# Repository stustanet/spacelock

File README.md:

# Spacelock

StuStaNet Hackerspace Lock

# Firmware build instructions

The spacelock firmware can be configured for several use cases.

For each use case there is a config file in firmware/build_config.

In order to activate a config, `ln -s` the chosen config file to firmware/src/config.h

# How to adapt the config to your usecase

The firmware can be easily adapted to your hardware setup via the config file.
See [# Firmware build instructions] for more details on how to build.

Be aware that many parameters use "u" to indicate that the parameters decimal point is shifted by 1.000.000 this is done to prevent floating point operations. 

At most places where you see UREVS in the code, UREVS of the key are meanted.
`#define ENDSTOP_DEAD_WINDOW_UREVS 100'000` is one 10th of a key revolution.

## Feature Configuration
 You can decide how you want to use the spacelock board. Below are to configuraiton examples

### 1. Secure Door Unlocking via QR Code Sensor (StuSta)
In this case the board is autonomous and installed in combination with a UART QR-Code reader (`#define WITH_QRCODE`). The authentication happens via a web service and the unlock cmd is a HMAC signed QR-Code. In order to prevent e.g. replay attacks. The QR-Code holds a timestamp, and is only for valid for a limited time. Therefore an external time source is needed. In this case DCF77 this is. To prevent unwanted access set (`#define WITH_BACKDOOR 0`)

 ### 2. Unsecure UART Unlocking with Door Sensor (Biederstein)
In this case the board is controlled from a raspberry pi via UART. 
The raspberry pi does all the authorization and simply requests to open the door via UART with "open". To enable this functionality `#define WITH_BACKDOOR 1`. Furthermore a door sensor is used to check if the door is open and lock it, when it's closed (`#define WITH_DOOR_SENSOR 1`).  

## Motor Configuration
The motor should be any stepper that can be driven by the DRV8266.
The relevant motor parameters are:
- UREVS_PER_STEP eg. (1.000.000 / 200) for a motor that has 200 steps per revolution 
- MOTOR_REVS_TO_UKEY_REVS e.g. 4.000.000 for a 4:1 ratio (4 rotations of the motor is one rotation of the key)
    if you have a gearing between motor and key you can but the ratio hear.
- ENDSTOP_DEAD_WINDOW_UREVS e.g. 100'000 ignore the current for the first 10th of a key rotation (starting current)

## Lock Configuration
- UNLOCKING_UREVS maximum distance the key has to travel to turn from totally locked to unlocked
- UNLOCK_SPEED_UREVS_PER_SEC unlocking search speed in µrev/s (until a resistance is found)
- UNLOCK_FINAL_SPEED_UREVS_PER_SEC final unlocking speed in µrev/s 
- UNLOCK_HOLD_DELAY_US time to hold the lock open in µs. In our case the doors are spring loaded and will automatically swing open, when unlocked.
- UNLOCK_BACKING_UREVS µRevolutions to back the key up so the door is no longer forced open
- ENDSTOP_ROTATE_AFTER_EDGE_UREVS how far the key is to be turned after a resistance is found in µRevolutions.
- FORCE_UNLOCK_UREVS how far the key is to be forcefully turned in case gracefull unlocking fails in µRevolutions. The key is assumed to be allready close to the resistance. Thus, this should be not much more than ENDSTOP_ROTATE_AFTER_EDGE_UREVS.

## Locking Parameters
- LOCK_DELAY how long to wait until a closed door is locked (!!!TODO!!!) 
be ware something is broken here!!! in my experience a value of 5.000.000.000 relates to about 8 sec of delay.
- LOCKING_UREVS how far to lock e.g. 2 revolutions given in µRevolutions
- LOCKING_SPEED_UREVS_PER_SEC locking speed in µrev/s

## Door Sensor
- DOOR_OPEN_STATE either true or false depending on your sensor (default open, default closed)
- DOOR_PORT where you connected the sensor
- DOOR_PIN which pin you connected the sensor (be aware that the default location GPIOA PIN8 clashes with the DCF77)

## Edge Detection
These parameters depend on your motor and are best found by testing. You can use the debug output (`#define WITH_DEBUG_OUTPUT 1` and see hardware.cpp line 283) and the process_data.py to stream live current measurements into a csv and monitor it with e.g. PlotJuggler.

- EDGE_DETECTION_THRESHOLD_UA how many µA the current has to rise in order to be detected as an edge
- EDGE_STEEPNESS_THRESHOLD_A_PER_S how fast the current has to rise in A/s
- FALLING_EDGE_HEIGHT_RESET_THRESHOLD_RATIO This needs some explanation. The idea is that in theory we would only like to detect one continous edge and reset as soon as the current is dropping again. However sometimes there is a small drop in the current, but then it increases further. Actually this should be covered by EDGE_STEEPNESS_THRESHOLD_A_PER_S and should be removed in the future. For now a number of e.g. 4 means, that the edge is reset as soon as there is a 1/4 decrease from the previous max edge height. 

Apart from the edge detection there is also an current integral. power = current * voltage. Thus we use the current to estimate the power drawn from the motor and its integral to compute the dumped energy. This feature basically prevents the motor from drawing too much power for too much time. 
- IT_INTEGRAL_DECAY_UA basically gives the power draw in normal operation, any excess current is then cumulated
- IT_INTEGRAL_THRESHOLD_UA_US a "energy" threshold in µA µs for the endstop detector

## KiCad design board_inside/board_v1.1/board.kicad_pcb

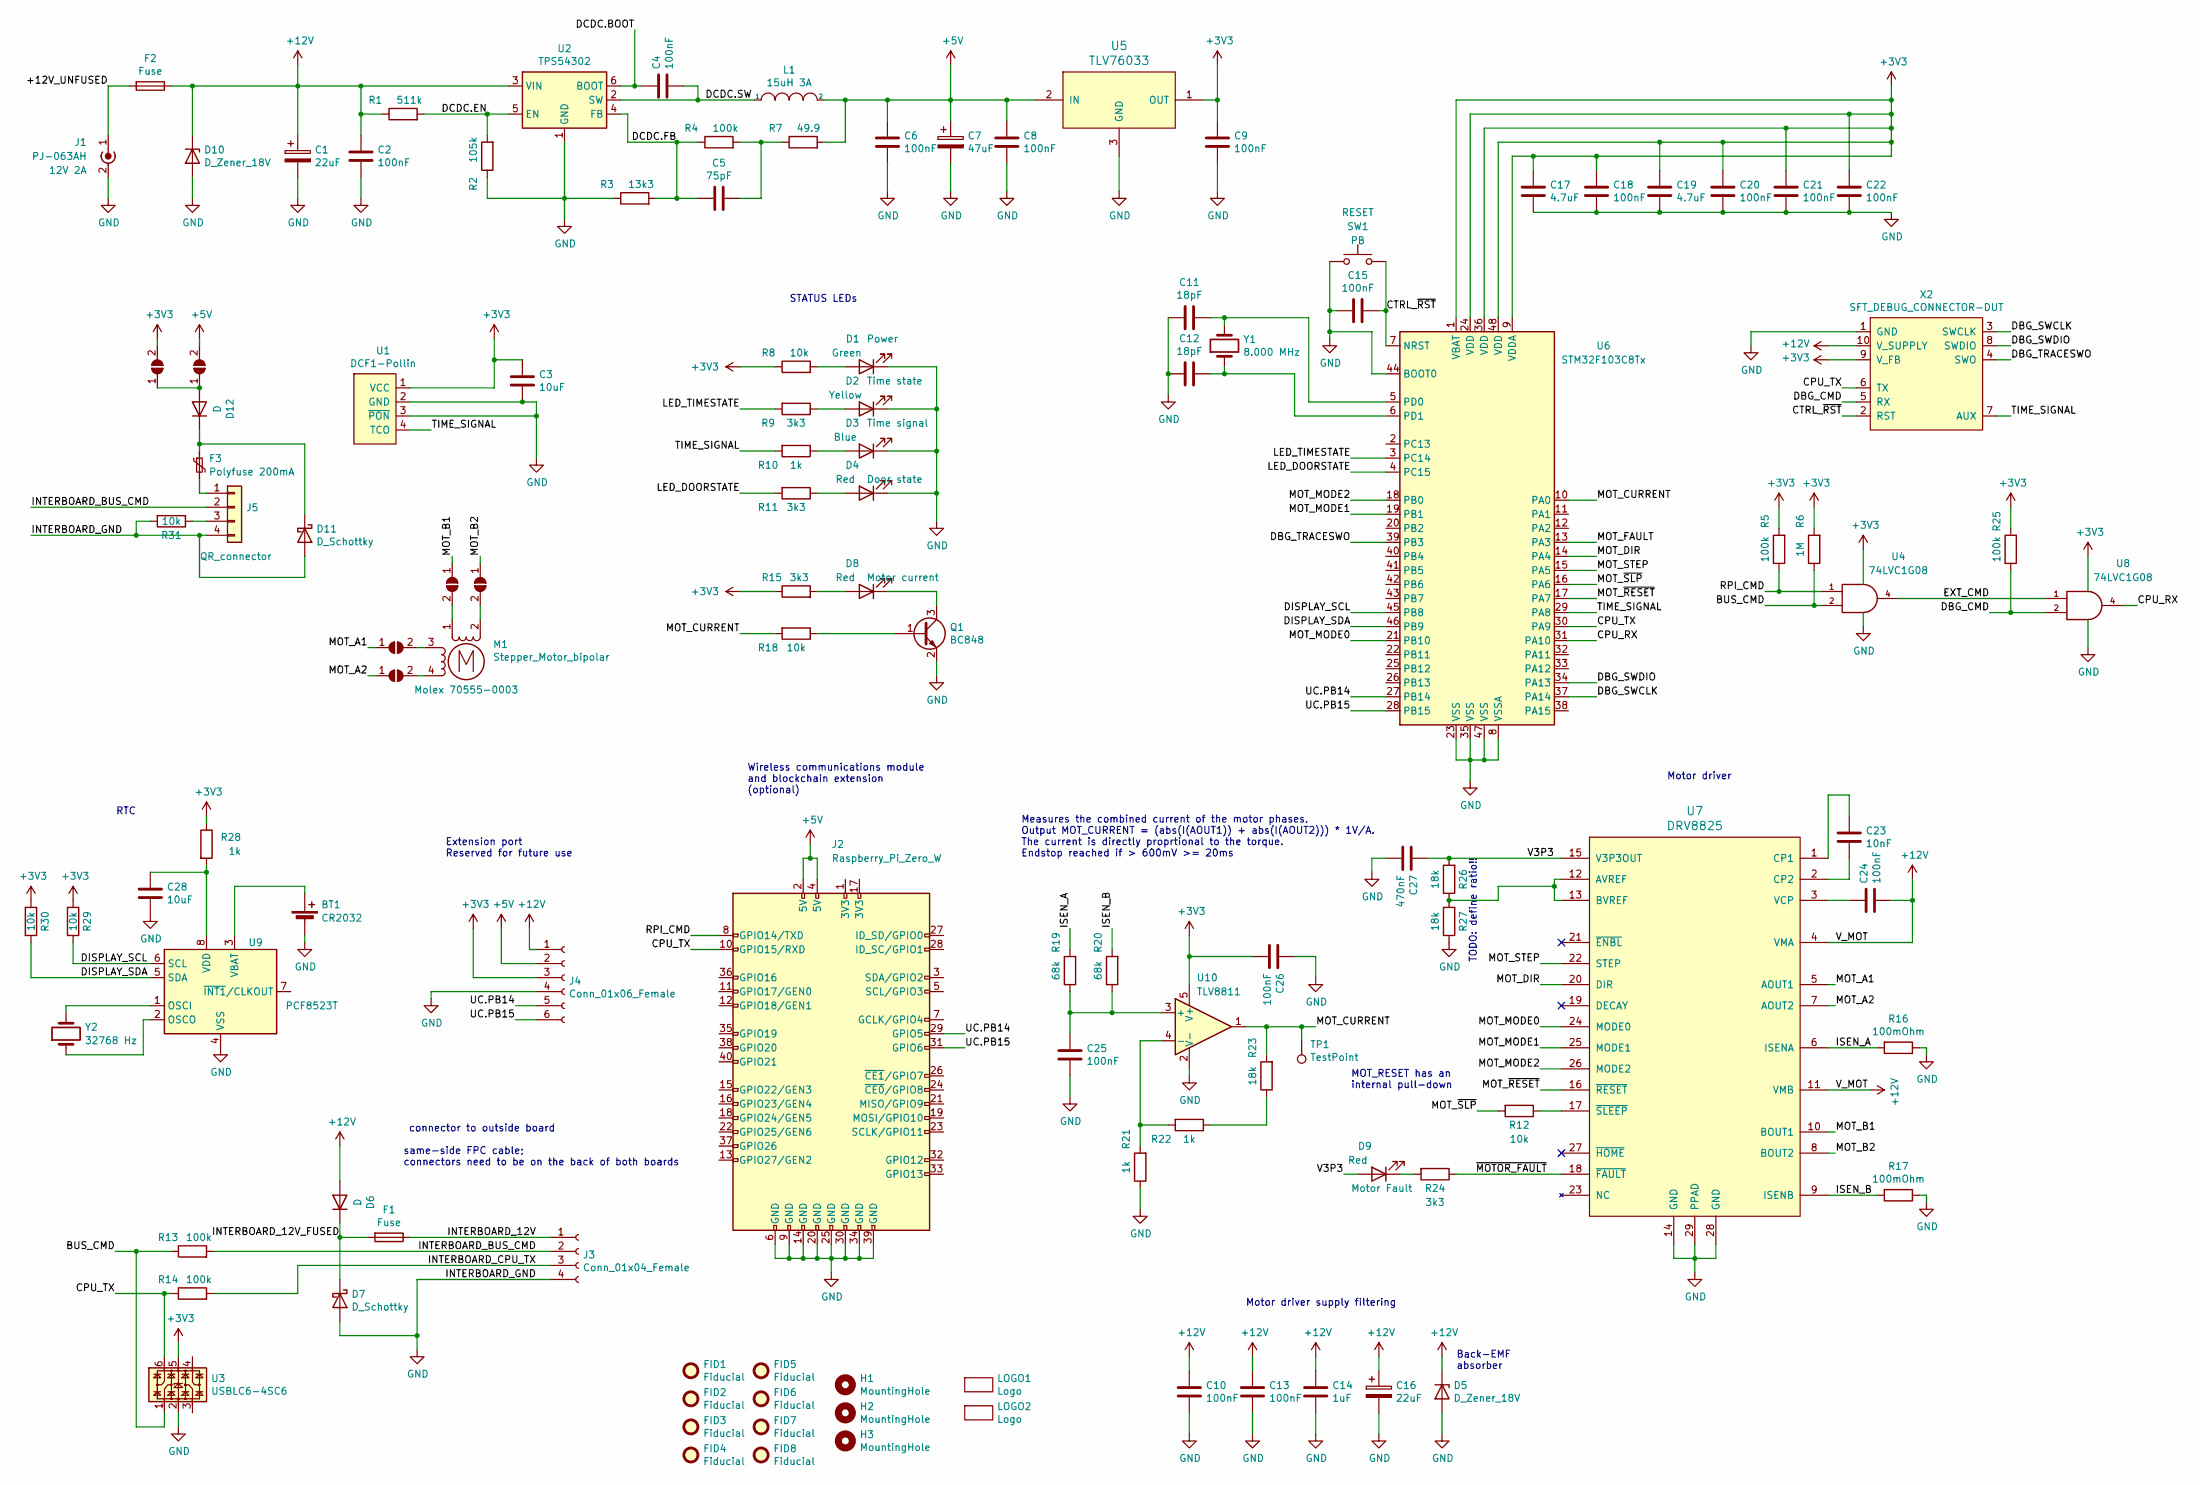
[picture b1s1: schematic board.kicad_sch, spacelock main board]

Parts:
BT1: CR2032; BatteryHolder_Keystone_3000_1x12mm; MPN Keystone 3000
C1, C16: 22uF; C_1206_3216Metric_Pad1.33x1.80mm_HandSolder; Rating 25V; MPN generic C%f %v %r
C2, C4, C6, C8, C9, C10, C13, C15, C18, C20, C21, C22, C24, C25, C26: 100nF; C_0603_1608Metric_Pad1.08x0.95mm_HandSolder; MPN generic C%f %v %r
C3, C28: 10uF; C_0603_1608Metric_Pad1.08x0.95mm_HandSolder; Rating 6.3V; MPN generic C%f %v %r
C5: 75pF; C_0603_1608Metric_Pad1.08x0.95mm_HandSolder; MPN generic C%f %v %r
C7: 47uF; C_1206_3216Metric_Pad1.33x1.80mm_HandSolder; Rating 6.3V; MPN generic C%f %v %r
C11, C12: 18pF; C_0603_1608Metric_Pad1.08x0.95mm_HandSolder; MPN generic C%f %v %r
C14: 1uF; C_0603_1608Metric_Pad1.08x0.95mm_HandSolder; MPN generic C%f %v %r
C17, C19: 4.7uF; C_0603_1608Metric_Pad1.08x0.95mm_HandSolder; Rating 6.3V; MPN generic C%f %v %r
C23: 10nF; C_0603_1608Metric_Pad1.08x0.95mm_HandSolder; MPN generic C%f %v %r
C27: 470nF; C_0603_1608Metric_Pad1.08x0.95mm_HandSolder; Rating 6.3V; MPN generic C%f %v %r
D1: Green; LED_0805_2012Metric_Pad1.15x1.40mm_HandSolder; MPN Wuerth 150080GS75000
D2: Yellow; LED_0805_2012Metric_Pad1.15x1.40mm_HandSolder; MPN Wuerth 150080YS75000
D3: Blue; LED_0805_2012Metric_Pad1.15x1.40mm_HandSolder; MPN Wuerth 150080BS75000
D4, D8, D9: Red; LED_0805_2012Metric_Pad1.15x1.40mm_HandSolder; MPN Wuerth 150080RS75000
D5, D10: D_Zener_18V; D_MiniMELF_Handsoldering; MPN generic ZMM5248B
D6, D12: D; D_SMB; MPN Rectron HFM208-W
D7, D11: D_Schottky; D_SOD-123; MPN Rectron 2SS100L-W
F1, F2: Fuse; Schurter-OGN-SMD; MPN Schurter OGN SMD
F3: Polyfuse 200mA; R_1210_3225Metric; MPN Littlefuse 1206L020YR
FID1, FID2, FID3, FID4, FID5, FID6, FID7, FID8: Fiducial; Fiducial_1mm_Mask2mm
H1, H2, H3: MountingHole; MountingHole_3.2mm_M3
J1: PJ-063AH; BarrelJack_CUI_PJ-063AH_Horizontal; MPN CUI PJ-063AH
J2: Raspberry_Pi_Zero_W; Raspberry_Pi_Zero_Socketed_THT_FaceDown_MountingHoles
J3: Conn_01x04_Female; Wuerth-686104188622; MPN Wuerth 686104188622
J4: Conn_01x06_Female; PinSocket_1x06_P2.54mm_Vertical
J5: QR_connector; PinHeader_1x04_P2.54mm_Vertical; MPN generic header-2.54mm
JP1, JP2, JP3, JP4, JP5, JP6: SolderJumper_2_Open; SolderJumper-2_P1.3mm_Open_TrianglePad1.0x1.5mm
L1: 15uH 3A; SRN8040TA; MPN Bourns SRN8040TA-150M
LOGO1: Logo; LOGO
LOGO2: Logo; LOGO_CU_070
M1: Stepper_Motor_bipolar; Molex-70555-0003; MPN Molex 70555-0003
Q1: BC848; SOT-23; MPN generic BC848B
R1: 511k; R_0603_1608Metric_Pad0.98x0.95mm_HandSolder; MPN generic R%f %v %r
R2: 105k; R_0603_1608Metric_Pad0.98x0.95mm_HandSolder; MPN generic R%f %v %r
R3: 13k3; R_0603_1608Metric_Pad0.98x0.95mm_HandSolder; MPN generic R%f %v %r
R4, R5, R13, R14, R25: 100k; R_0603_1608Metric_Pad0.98x0.95mm_HandSolder; MPN generic R%f %v %r
R6: 1M; R_0603_1608Metric_Pad0.98x0.95mm_HandSolder; MPN generic R%f %v %r
R7: 49.9; R_0603_1608Metric_Pad0.98x0.95mm_HandSolder; MPN generic R%f %v %r
R8, R12, R18, R29, R30, R31: 10k; R_0603_1608Metric_Pad0.98x0.95mm_HandSolder; MPN generic R%f %v %r
R9, R11, R15, R24: 3k3; R_0603_1608Metric_Pad0.98x0.95mm_HandSolder; MPN generic R%f %v %r
R10, R21, R22, R28: 1k; R_0603_1608Metric_Pad0.98x0.95mm_HandSolder; MPN generic R%f %v %r
R16, R17: 100mOhm; R_2512_6332Metric; MPN Yageo PT2512FK-7W0R1L
R19, R20: 68k; R_0603_1608Metric_Pad0.98x0.95mm_HandSolder; MPN generic R%f %v %r
R23, R26, R27: 18k; R_0603_1608Metric_Pad0.98x0.95mm_HandSolder; MPN generic R%f %v %r
SW1: PB; SW_PUSH_6mm_H4.3mm; MPN Panasonic EVQPAE05R
TP1: TestPoint; TestPoint_Pad_D1.5mm
U1: DCF1-Pollin; MPN Pollin DCF1
U2: TPS54302; SOT-23-6; MPN TI TPS54302DDC
U3: USBLC6-4SC6; SOT-23-6; MPN ST USBLC6-4SC6
U4, U8: 74LVC1G08; SOT-23-5_HandSoldering; MPN TI 74LVC1G08DBV
U5: TLV76033; SOT-23; MPN TI TLV76033DBZ
U6: STM32F103C8Tx; LQFP-48_7x7mm_P0.5mm; MPN ST STM32F103C8T6
U7: DRV8825; HTSSOP-28-1EP_4.4x9.7mm_P0.65mm_EP3.4x9.5mm_ThermalVias; MPN TI DRV8825PWP
U9: PCF8523T; SOIC-8_3.9x4.9mm_P1.27mm; MPN NXP PCF8523T
U10: TLV8811; SOT-23-5_HandSoldering; MPN TI TLV8811DBV
X2: SFT_DEBUG_CONNECTOR-DUT; Tag-Connect_TC2050-IDC-FP_2x05_P1.27mm_Vertical
Y1: 8.000 MHz; Crystal_HC49-U_Vertical; MPN ZheJiang B08000J065
Y2: 32768 Hz; Crystal_SMD_EuroQuartz_EQ161-2Pin_3.2x1.5mm_HandSoldering; MPN MicroCrystal CM7V-T1A-LOW-ESR-32.768KHZ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

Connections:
+3V3: C3.1, C9.1, C17.1, C18.1, C19.1, C20.1, C21.1, C22.1, C26.2, J4.3, JP6.2 (B), R5.2, R6.2, R8.1, R15.1, R25.2, R28.1, R29.1, R30.1, U1.1 (VCC), U3.5, U4.5 (VCC), U5.1 (OUT), U6.1 (VBAT), U6.9 (VDDA), U6.24 (VDD), U6.36 (VDD), U6.48 (VDD), U8.5 (VCC), U10.5 (V+), X2.9 (V_FB)
+5V: C6.1, C7.1, C8.1, J2.2 (5V), J2.4 (5V), J4.2, JP5.2 (B), L1.2, R7.2, U5.2 (IN)
+12V: C1.1, C2.1, C10.1, C13.1, C14.1, C16.1, C24.2, D5.1 (K), D6.2 (A), D10.1 (K), F2.1, J4.1, R1.1, U2.3 (VIN), U7.4 (VMA), U7.11 (VMB), X2.10 (V_SUPPLY)
/+12V_UNFUSED: F2.2, J1.1 (In)
/BUS_CMD: R6.1, R13.1, U3.1, U4.2
/CPU_RX: U6.31 (PA10), U8.4
/CPU_TX: J2.10 (GPIO15/RXD), R14.1, U3.6, U6.30 (PA9), X2.6 (TX)
/CTRL_~RST: C15.1, SW1.2, U6.7 (NRST), X2.2 (RST)
/DBG_CMD: R25.1, U8.2, X2.5 (RX)
/DBG_SWCLK: U6.37 (PA14), X2.3 (SWCLK)
/DBG_SWDIO: U6.34 (PA13), X2.8 (SWDIO)
/DBG_TRACESWO: U6.39 (PB3), X2.4 (SWO)
/DCDC.BOOT: C4.1, U2.6 (BOOT)
/DCDC.EN: R1.2, R2.2, U2.5 (EN)
/DCDC.FB: C5.2, R3.2, R4.1, U2.4 (FB)
/DCDC.SW: C4.2, L1.1, U2.2 (SW)
/DISPLAY_SCL: R29.2, U6.45 (PB8), U9.6 (SCL)
/DISPLAY_SDA: R30.2, U6.46 (PB9), U9.5 (SDA)
/EXT_CMD: U4.4, U8.1
/INTERBOARD_12V: F1.1, J3.1
/INTERBOARD_12V_FUSED: D6.1 (K), D7.1 (K), F1.2
/INTERBOARD_BUS_CMD: J3.2, J5.2, R13.2
/INTERBOARD_CPU_TX: J3.3, R14.2
/ISEN_A: R16.2, R19.2, U7.6 (ISENA)
/ISEN_B: R17.2, R20.2, U7.9 (ISENB)
/LED_DOORSTATE: R11.2, U6.4 (PC15)
/LED_TIMESTATE: R9.2, U6.3 (PC14)
/MOT_A1: JP1.1 (A), U7.5 (AOUT1)
/MOT_A2: JP2.1 (A), U7.7 (AOUT2)
/MOT_B1: JP3.1 (A), U7.10 (BOUT1)
/MOT_B2: JP4.1 (A), U7.8 (BOUT2)
/MOT_CURRENT: R18.2, R23.2, TP1.1, U6.10 (PA0), U10.1
/MOT_DIR: U6.14 (PA4), U7.20 (DIR)
/MOT_FAULT: U6.13 (PA3)
/MOT_MODE0: U6.21 (PB10), U7.24 (MODE0)
/MOT_MODE1: U6.19 (PB1), U7.25 (MODE1)
/MOT_MODE2: U6.18 (PB0), U7.26 (MODE2)
/MOT_STEP: U6.15 (PA5), U7.22 (STEP)
/MOT_~RESET: U6.17 (PA7), U7.16 (~RESET)
/MOT_~SLP: R12.2, U6.16 (PA6)
/RPI_CMD: J2.8 (GPIO14/TXD), R5.1, U4.1
/TIME_SIGNAL: R10.2, U1.4 (TCO), U6.29 (PA8), X2.7 (AUX)
/UC.PB14: J2.29 (GPIO5), J4.5, U6.27 (PB14)
/UC.PB15: J2.31 (GPIO6), J4.6, U6.28 (PB15)
/V3P3: C27.1, D9.2 (A), R26.2, U7.15 (V3P3OUT)
/~MOTOR_FAULT: R24.1, U7.18 (~FAULT)
GND: BT1.2 (-), C1.2, C2.2, C3.2, C6.2, C7.2, C8.2, C9.2, C10.2, C11.2, C12.2, C13.2, C14.2, C15.2, C16.2, C17.2, C18.2, C19.2, C20.2, C21.2, C22.2, C25.2, C26.1, C27.2, C28.2, D1.1 (K), D2.1 (K), D3.1 (K), D4.1 (K), D5.2 (A), D7.2 (A), D10.2 (A), D11.2 (A), J1.2 (Ext), J2.6 (GND), J2.9 (GND), J2.14 (GND), J2.20 (GND), J2.25 (GND), J2.30 (GND), J2.34 (GND), J2.39 (GND), J3.4, J4.4, J5.4, Q1.2 (E), R2.1, R3.1, R16.1, R17.1, R21.1, R27.1, R31.2, SW1.1, U1.2 (GND), U1.3 (~PON), U2.1 (GND), U3.2, U4.3 (GND), U5.3 (GND), U6.8 (VSSA), U6.23 (VSS), U6.35 (VSS), U6.44 (BOOT0), U6.47 (VSS), U7.14 (GND), U7.28 (GND), U7.29 (PPAD), U8.3 (GND), U9.4 (VSS), U10.2 (V-), X2.1 (GND)
unnamed: BT1.1 (+), U9.3 (VBAT)
unnamed: C5.1, R4.2, R7.1
unnamed: D1.2 (A), R8.2
unnamed: D2.2 (A), R9.1
unnamed: D3.2 (A), R10.1
unnamed: D4.2 (A), R11.1
unnamed: D8.2 (A), R15.2
unnamed: D8.1 (K), Q1.3 (C)
unnamed: D9.1 (K), R24.2
unnamed: D11.1 (K), D12.1 (K), F3.1
unnamed: D12.2 (A), JP5.1 (A), JP6.1 (A)
unnamed: F3.2, J5.1
unnamed: J5.3, R31.1
unnamed: JP1.2 (B), M1.3
unnamed: JP2.2 (B), M1.4
unnamed: JP3.2 (B), M1.1
unnamed: JP4.2 (B), M1.2 (-)
unnamed: Q1.1 (B), R18.1
unnamed: R22.1, R23.1
unnamed: C11.1, U6.5 (PD0), Y1.2
unnamed: C12.1, U6.6 (PD1), Y1.1
unnamed: R26.1, R27.2, U7.12 (AVREF), U7.13 (BVREF)
unnamed: C23.1, U7.1 (CP1)
unnamed: C23.2, U7.2 (CP2)
unnamed: C24.1, U7.3 (VCP)
unnamed: R12.1, U7.17 (~SLEEP)
unnamed: U9.1 (OSCI), Y2.2
unnamed: U9.2 (OSCO), Y2.1
unnamed: C28.1, R28.2, U9.8 (VDD)
unnamed: C25.1, R19.1, R20.1, U10.3 (+)
unnamed: R21.2, R22.2, U10.4 (-)

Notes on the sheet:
Measures the combined current of the motor phases. Output MOT_CURRENT = (abs(I(AOUT1)) + abs(I(AOUT2))) * 1V/A. The current is directly proprtional to the torque. Endstop reached if > 600mV >= 20ms
MOT_RESET has an internal pull-down
Back-EMF absorber
Extension port Reserved for future use
Motor driver supply filtering
STATUS LEDs
RTC
Wireless communications module and blockchain extension (optional)
Motor driver
TODO: define ratio!!
connector to outside board same-side FPC cable; connectors need to be on the back of both boards

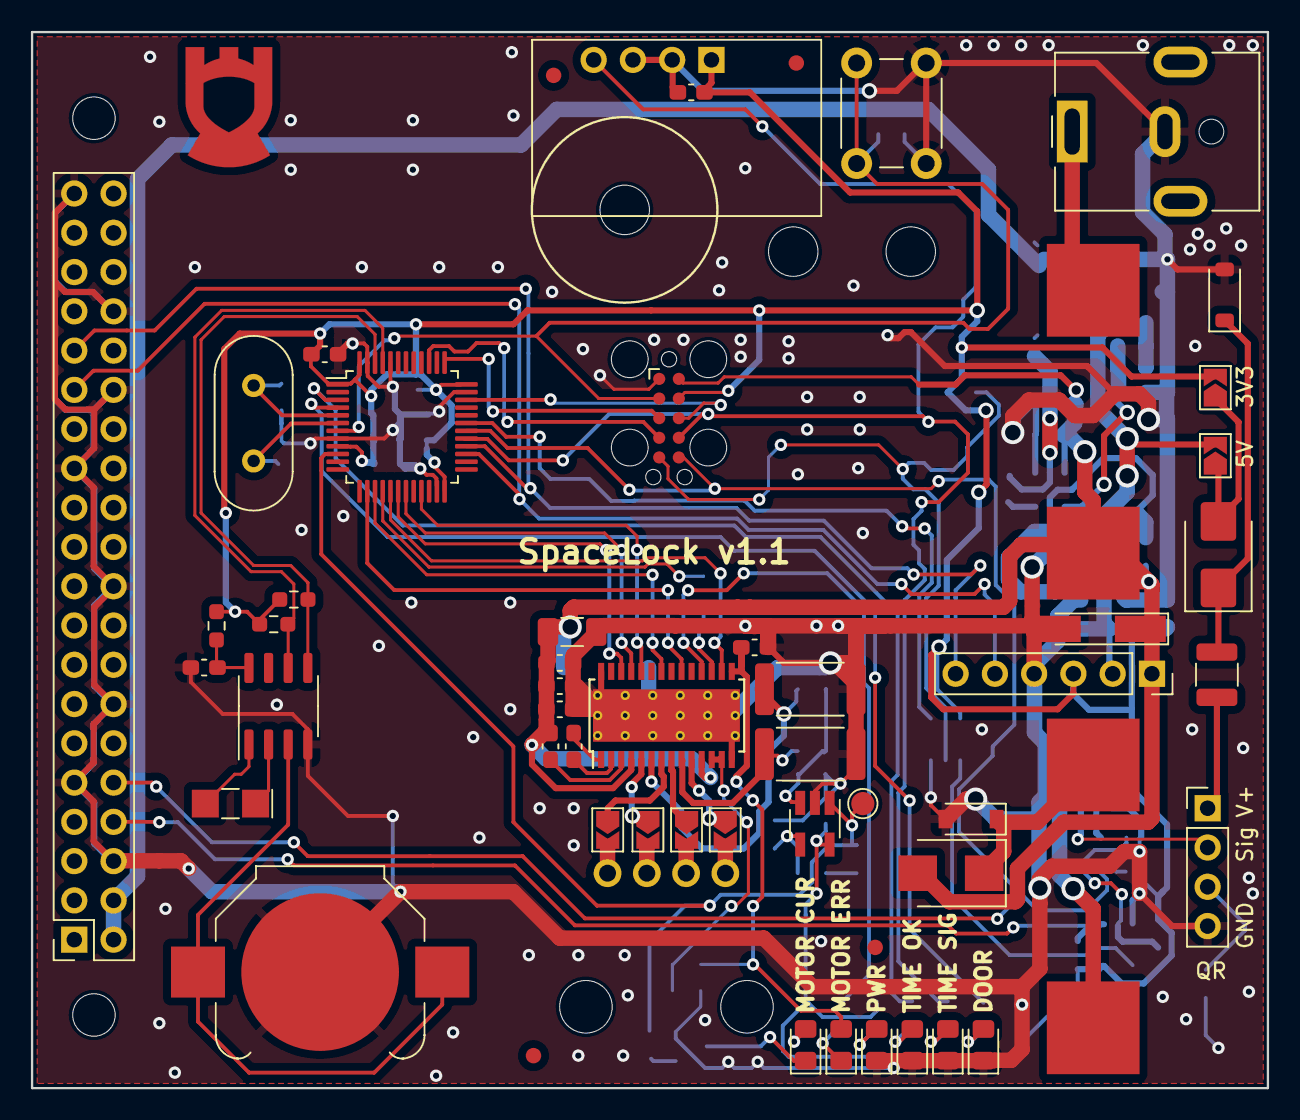
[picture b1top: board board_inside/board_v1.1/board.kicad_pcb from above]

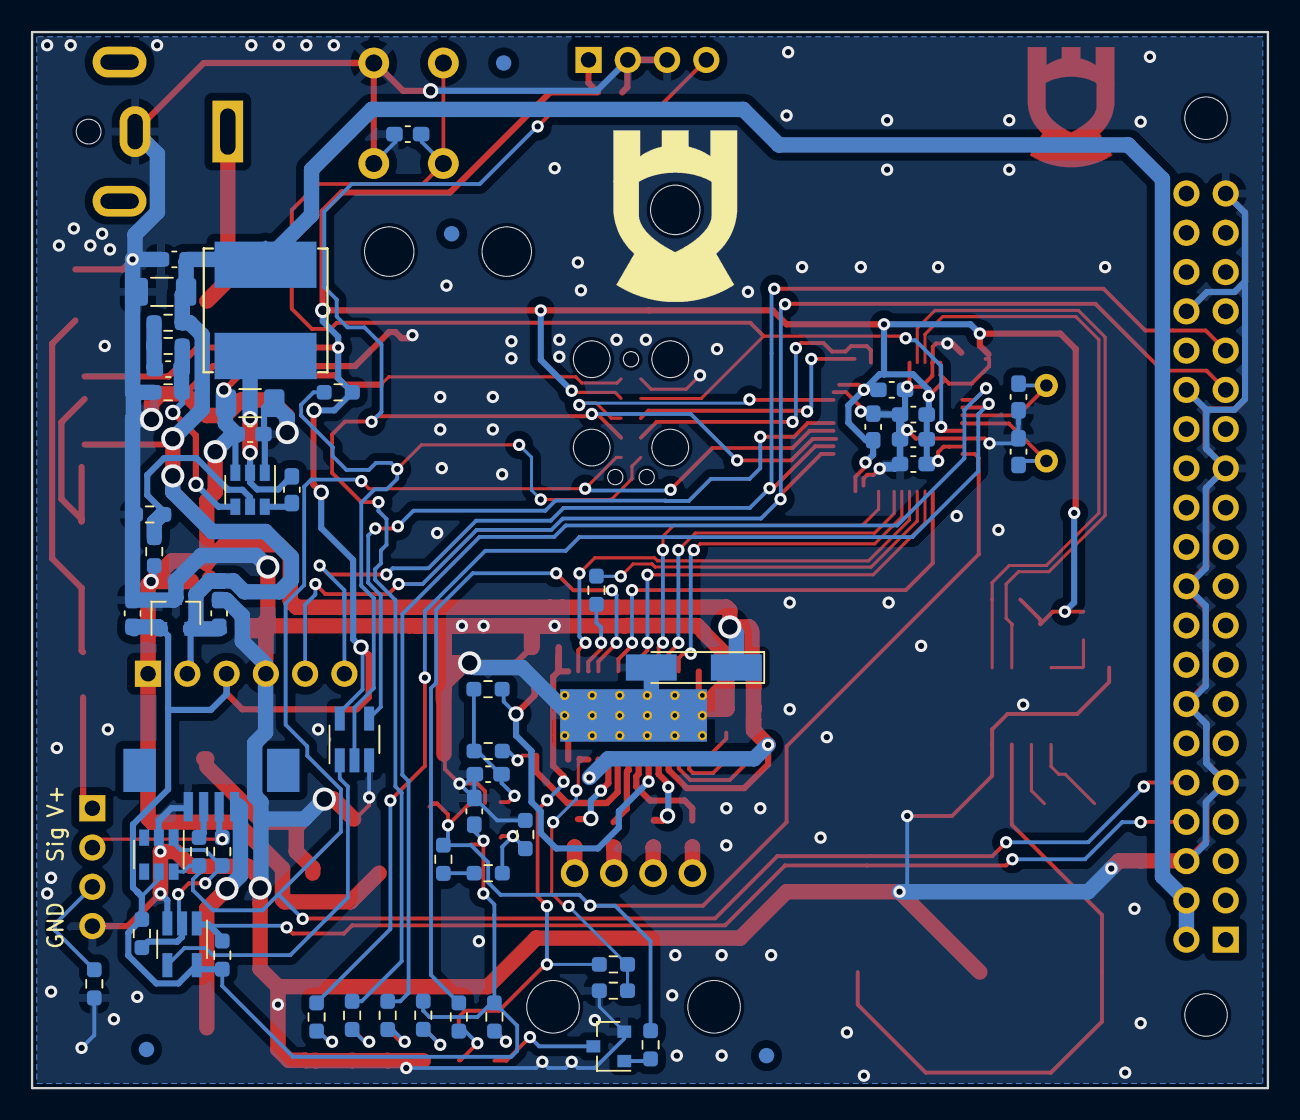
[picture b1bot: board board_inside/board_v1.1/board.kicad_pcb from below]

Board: 2 copper layers, 79.9 x 68.3 mm, 117 parts (58 on the bottom side), 77 nets.

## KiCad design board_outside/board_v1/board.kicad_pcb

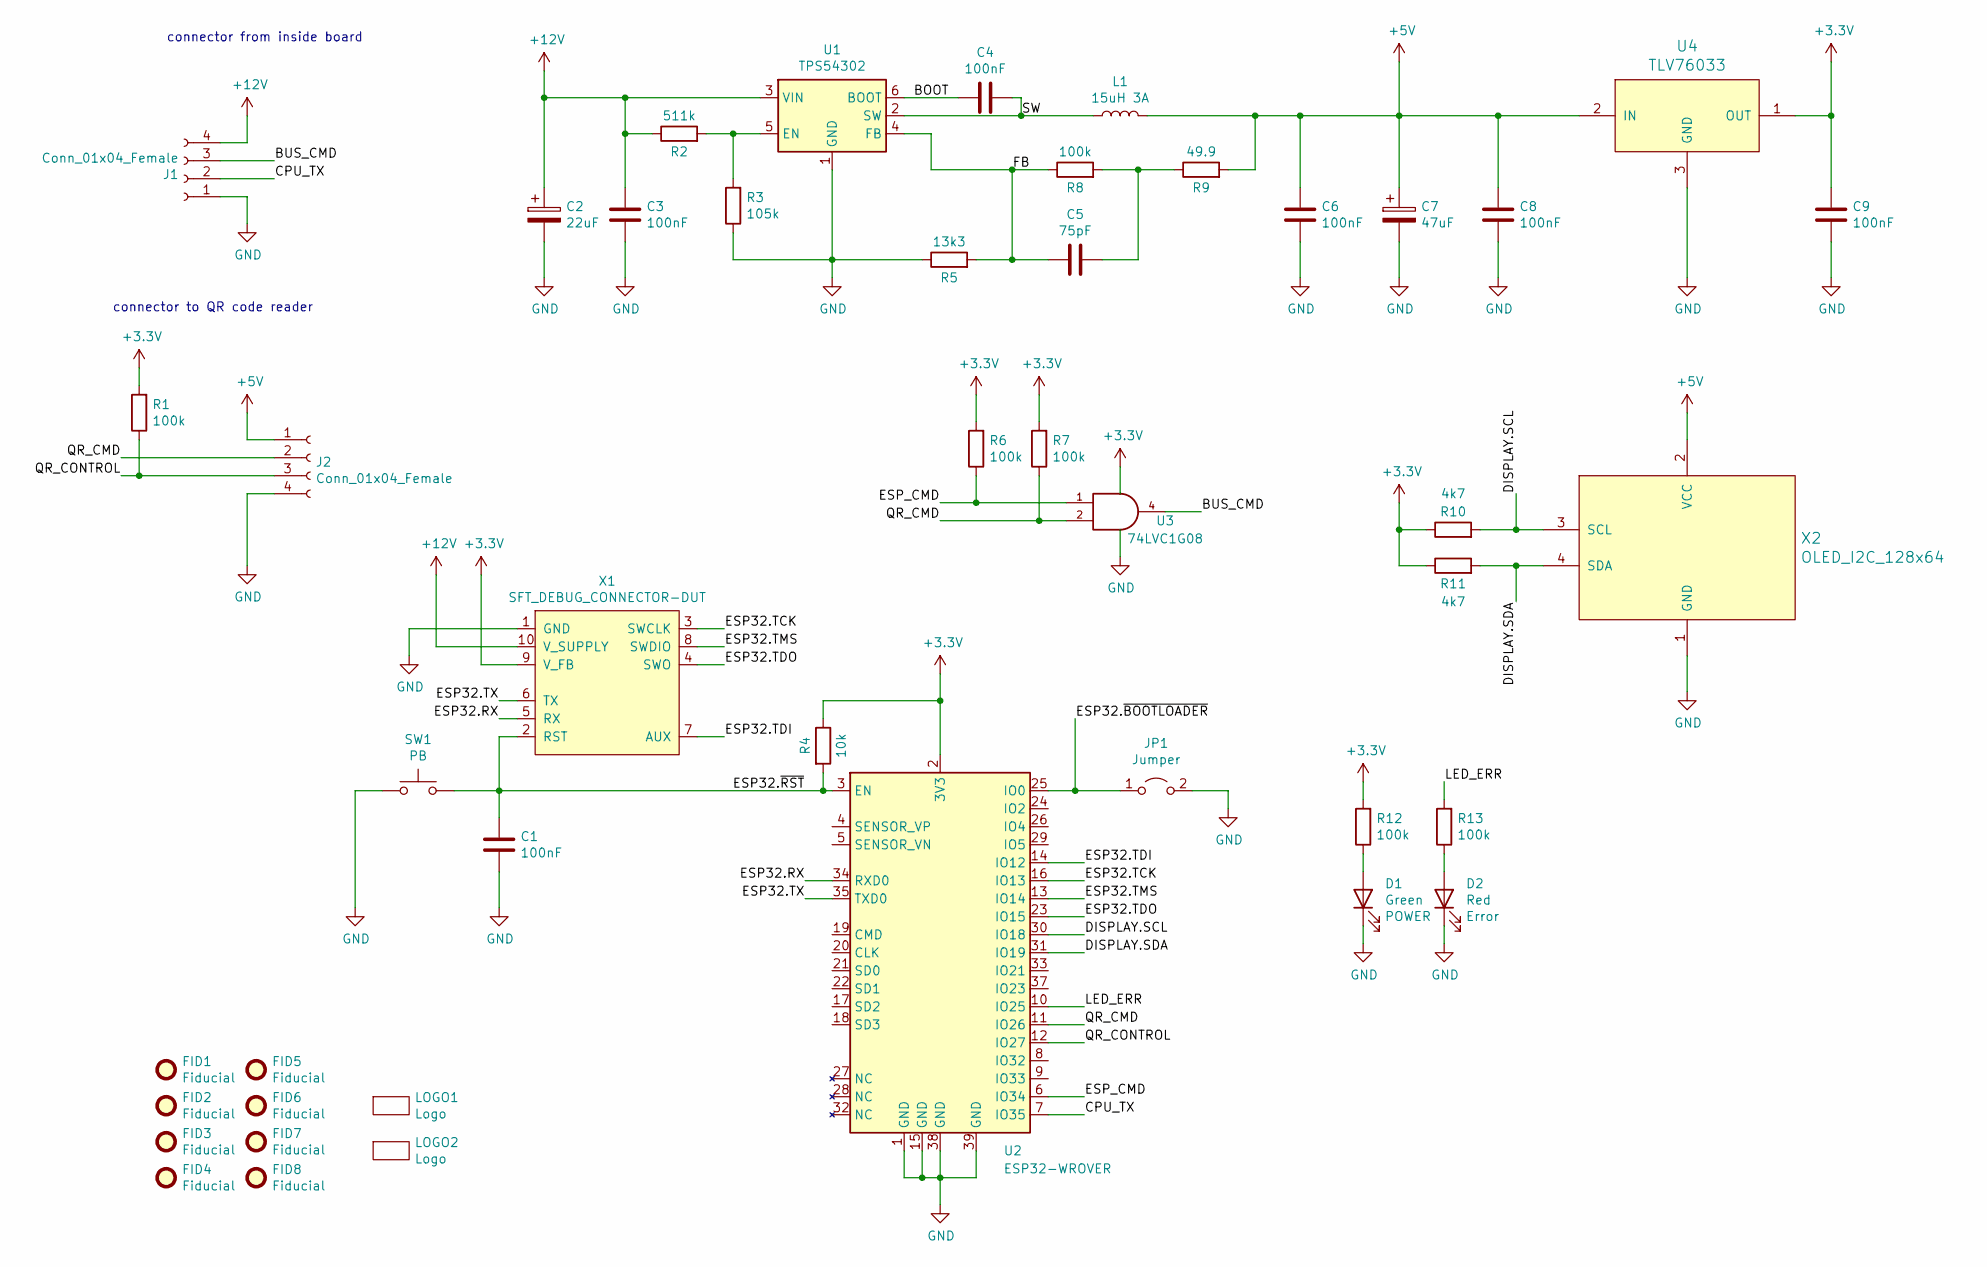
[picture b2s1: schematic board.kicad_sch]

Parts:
C1, C3, C4, C6, C8, C9: 100nF; C_0603_1608Metric_Pad1.08x0.95mm_HandSolder; MPN generic C%f %v %r
C2: 22uF; C_1206_3216Metric_Pad1.33x1.80mm_HandSolder; Rating 25V; MPN generic C%f %v %r
C5: 75pF; C_0603_1608Metric_Pad1.08x0.95mm_HandSolder; MPN generic C%f %v %r
C7: 47uF; C_1206_3216Metric_Pad1.33x1.80mm_HandSolder; Rating 6.3V; MPN generic C%f %v %r
D1: Green; LED_0805_2012Metric_Pad1.15x1.40mm_HandSolder; MPN Wuerth 150080GS75000
D2: Red; LED_0805_2012Metric_Pad1.15x1.40mm_HandSolder; MPN Wuerth 150080RS75000
FID1, FID2, FID3, FID4, FID5, FID6, FID7, FID8: Fiducial; Fiducial_1mm_Mask2mm
J1: Conn_01x04_Female; Wuerth-686104188622; MPN Wuerth 686104188622
J2: Conn_01x04_Female; PinSocket_1x04_P2.54mm_Vertical; MPN generic header-2.54mm
JP1: Jumper; PinHeader_1x02_P2.54mm_Vertical
L1: 15uH 3A; SRN8040TA; MPN Bourns SRN8040TA-150M
LOGO1: Logo; LOGO_CU_070
LOGO2: Logo; LOGO
R1, R6, R7, R8, R12, R13: 100k; R_0603_1608Metric_Pad0.98x0.95mm_HandSolder; MPN generic R%f %v %r
R2: 511k; R_0603_1608Metric_Pad0.98x0.95mm_HandSolder; MPN generic R%f %v %r
R3: 105k; R_0603_1608Metric_Pad0.98x0.95mm_HandSolder; MPN generic R%f %v %r
R4: 10k; R_0603_1608Metric_Pad0.98x0.95mm_HandSolder; MPN generic R%f %v %r
R5: 13k3; R_0603_1608Metric_Pad0.98x0.95mm_HandSolder; MPN generic R%f %v %r
R9: 49.9; R_0603_1608Metric_Pad0.98x0.95mm_HandSolder; MPN generic R%f %v %r
R10, R11: 4k7; R_0603_1608Metric_Pad0.98x0.95mm_HandSolder; MPN generic R%f %v %r
SW1: PB; SW_PUSH_6mm_H4.3mm; MPN Panasonic EVQPAE05R
U1: TPS54302; SOT-23-6; MPN TI TPS54302DDC
U2: ESP32-WROVER; MPN Espressif ESP32-WROVER
U3: 74LVC1G08; SOT-23-5_HandSoldering; MPN TI 74LVC1G08DBV
U4: TLV76033; SOT-23; MPN TI TLV76033DBZ
X1: SFT_DEBUG_CONNECTOR-DUT; Tag-Connect_TC2050-IDC-FP_2x05_P1.27mm_Vertical
X2: OLED_I2C_128x64; OLED_128x64_096in; MPN generic I2C-OLED-128x64

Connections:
+3V3: C9.1, R1.2, R4.1, R6.2, R7.2, R10.1, R11.1, R12.2, U2.2 (3V3), U3.5 (VCC), U4.1 (OUT), X1.9 (V_FB)
+5V: C6.1, C7.1, C8.1, J2.1, L1.2, R9.2, U4.2 (IN), X2.2 (VCC)
+12V: C2.1, C3.1, J1.4, R2.1, U1.3 (VIN), X1.10 (V_SUPPLY)
/BOOT: C4.2, U1.6 (BOOT)
/BUS_CMD: J1.3, U3.4
/CPU_TX: J1.2, U2.7 (IO35)
/DISPLAY.SCL: R10.2, U2.30 (IO18), X2.3 (SCL)
/DISPLAY.SDA: R11.2, U2.31 (IO19), X2.4 (SDA)
/ESP32.RX: U2.34 (RXD0), X1.5 (RX)
/ESP32.TCK: U2.16 (IO13), X1.3 (SWCLK)
/ESP32.TDI: U2.14 (IO12), X1.7 (AUX)
/ESP32.TDO: U2.23 (IO15), X1.4 (SWO)
/ESP32.TMS: U2.13 (IO14), X1.8 (SWDIO)
/ESP32.TX: U2.35 (TXD0), X1.6 (TX)
/ESP32.~BOOTLOADER: JP1.1 (A), U2.25 (IO0)
/ESP32.~RST: C1.1, R4.2, SW1.2, U2.3 (EN), X1.2 (RST)
/ESP_CMD: R6.1, U2.6 (IO34), U3.1
/FB: C5.2, R5.2, R8.1, U1.4 (FB)
/LED_ERR: R13.2, U2.10 (IO25)
/QR_CMD: J2.2, R7.1, U2.11 (IO26), U3.2
/QR_CONTROL: J2.3, R1.1, U2.12 (IO27)
/SW: C4.1, L1.1, U1.2 (SW)
GND: C1.2, C2.2, C3.2, C6.2, C7.2, C8.2, C9.2, D1.1 (K), D2.1 (K), J1.1, J2.4, JP1.2 (B), R3.1, R5.1, SW1.1, U1.1 (GND), U2.1 (GND), U2.15 (GND), U2.38 (GND), U2.39 (GND), U3.3 (GND), U4.3 (GND), X1.1 (GND), X2.1 (GND)
unnamed: C5.1, R8.2, R9.1
unnamed: D1.2 (A), R12.1
unnamed: D2.2 (A), R13.1
unnamed: R2.2, R3.2, U1.5 (EN)

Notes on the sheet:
connector to QR code reader
connector from inside board

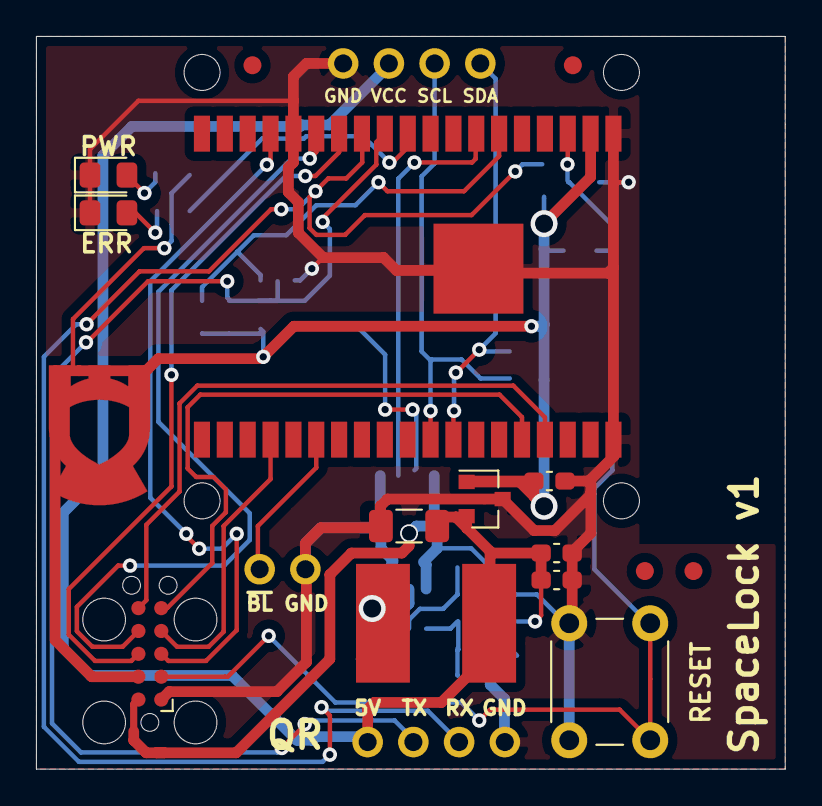
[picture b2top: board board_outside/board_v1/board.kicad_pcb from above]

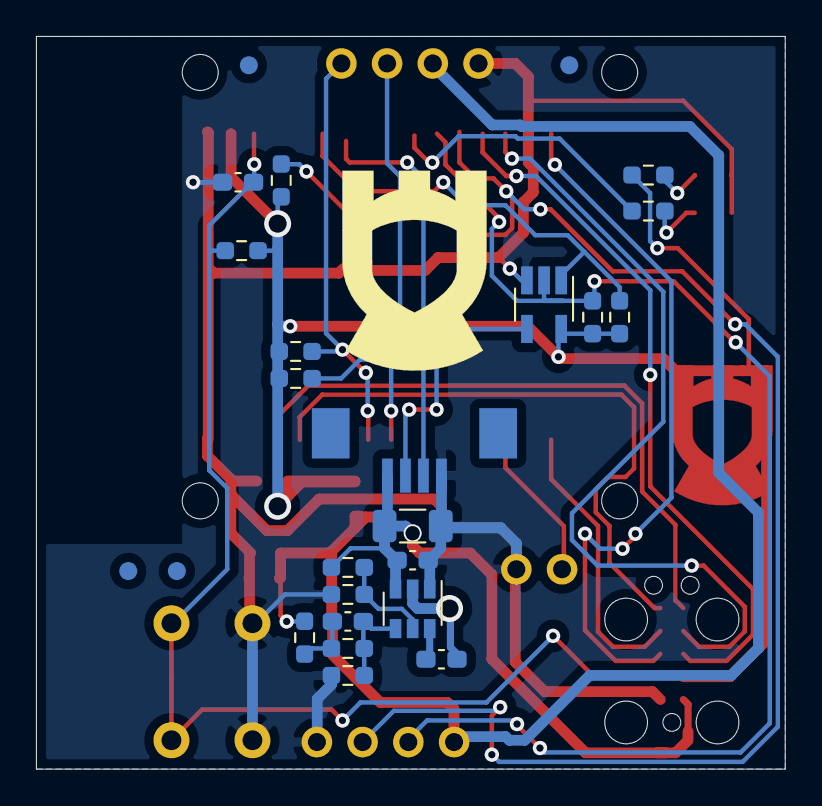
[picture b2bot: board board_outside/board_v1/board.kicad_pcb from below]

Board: 2 copper layers, 41.6 x 40.7 mm, 45 parts (26 on the bottom side), 27 nets.
